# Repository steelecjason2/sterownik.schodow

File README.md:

16 stairs LED controller, and it's easy to extend by connecting just few wires to next TLC5940 PWM LED driver. 

parts not listed in schematics:

2x E18-D80NK Sensor Proximity 3-80cm,

2x microswitches, normal open.

SANPU 12VDC Waterproof LED Power Supply 12V DC 120W 10A IP67

Bluetooth HC-05

LED Strip 12V

PGM5516 photoresistor

2x potentiometer 10k multi-turn type 3/8''

https://www.youtube.com/watch?v=NjSVoOenioQ

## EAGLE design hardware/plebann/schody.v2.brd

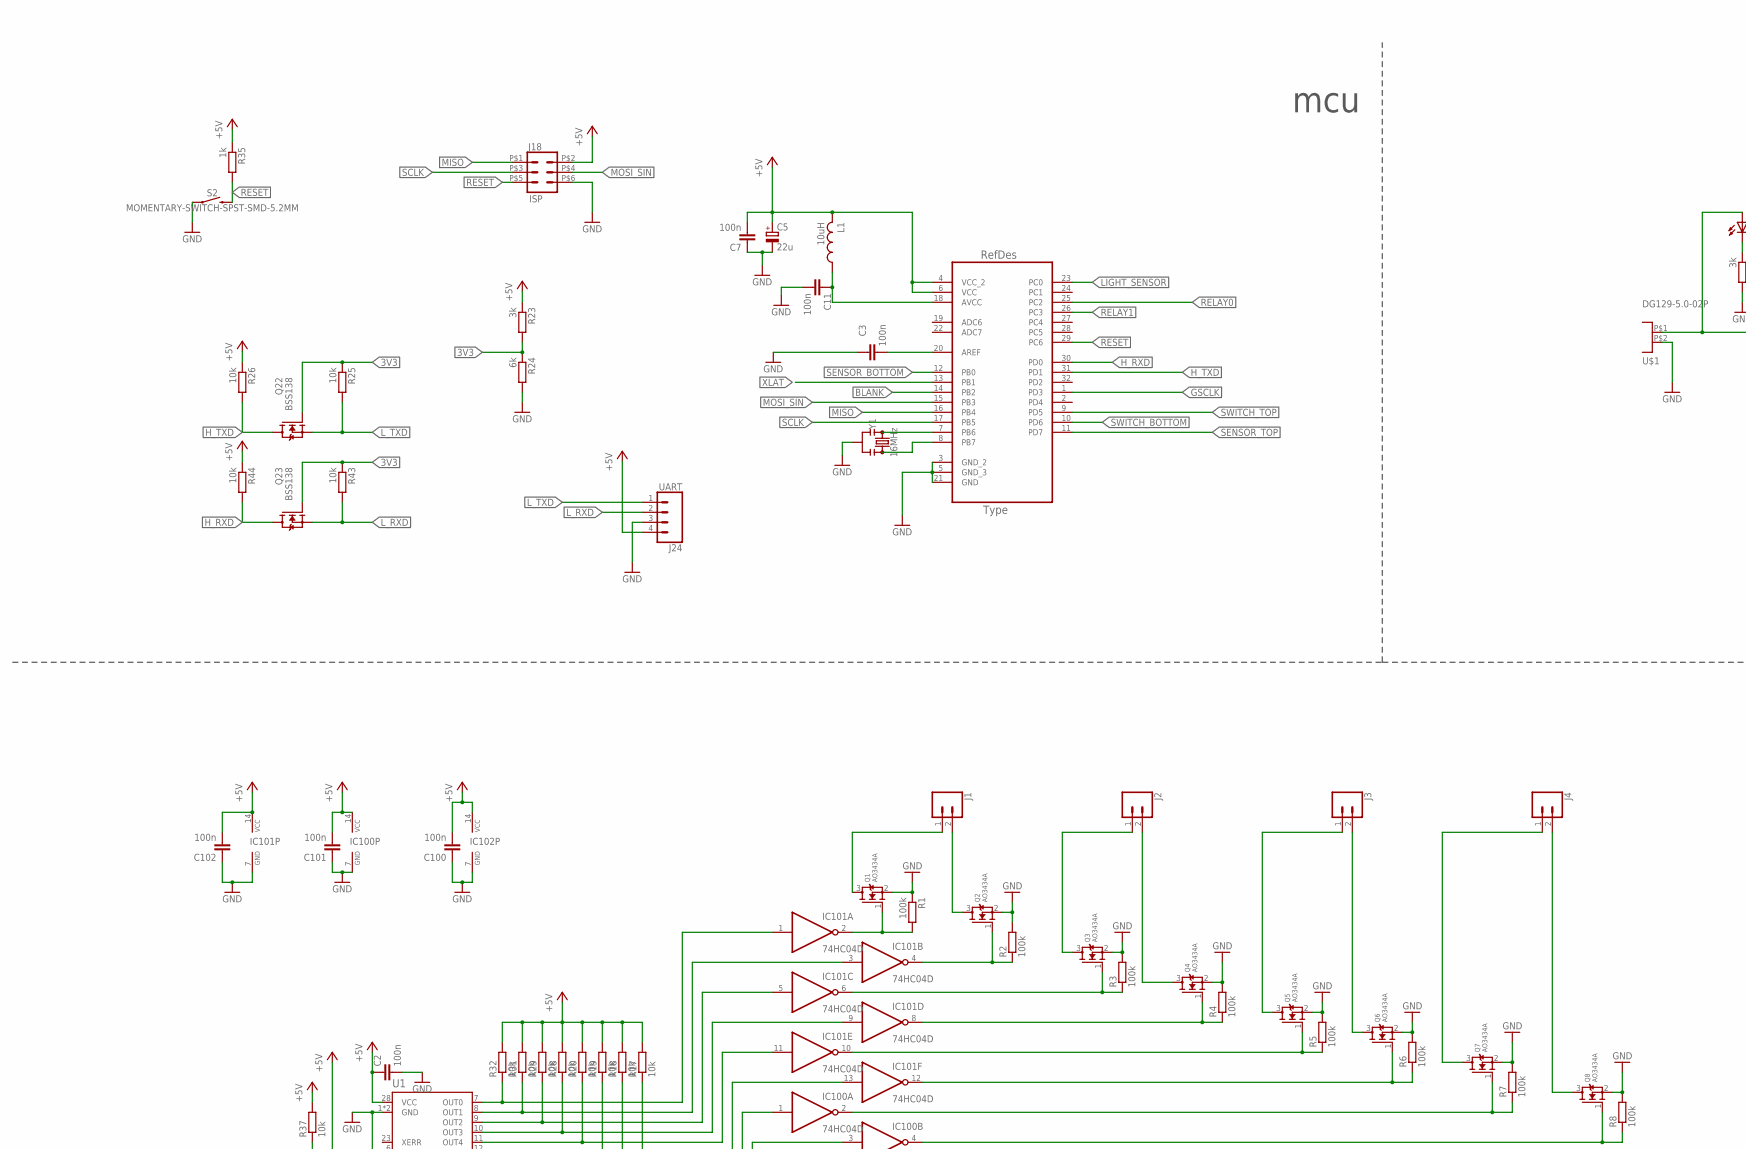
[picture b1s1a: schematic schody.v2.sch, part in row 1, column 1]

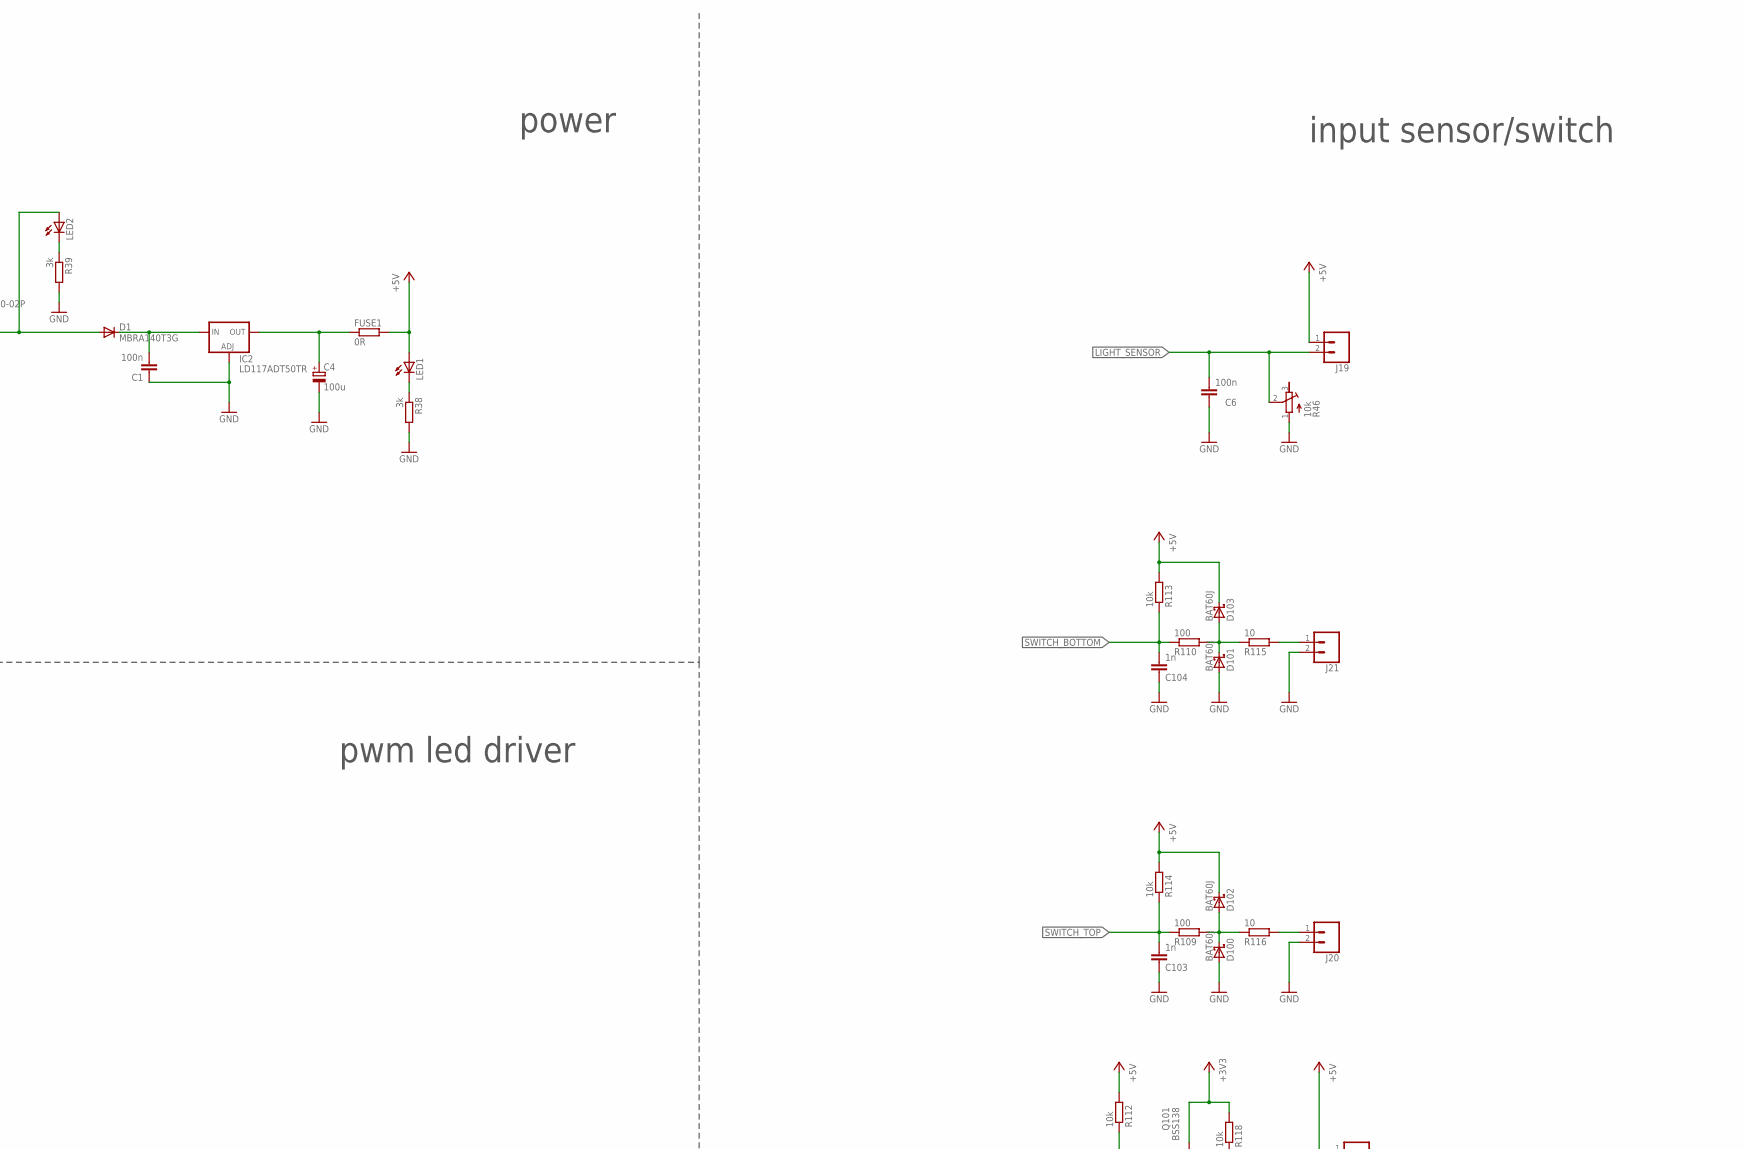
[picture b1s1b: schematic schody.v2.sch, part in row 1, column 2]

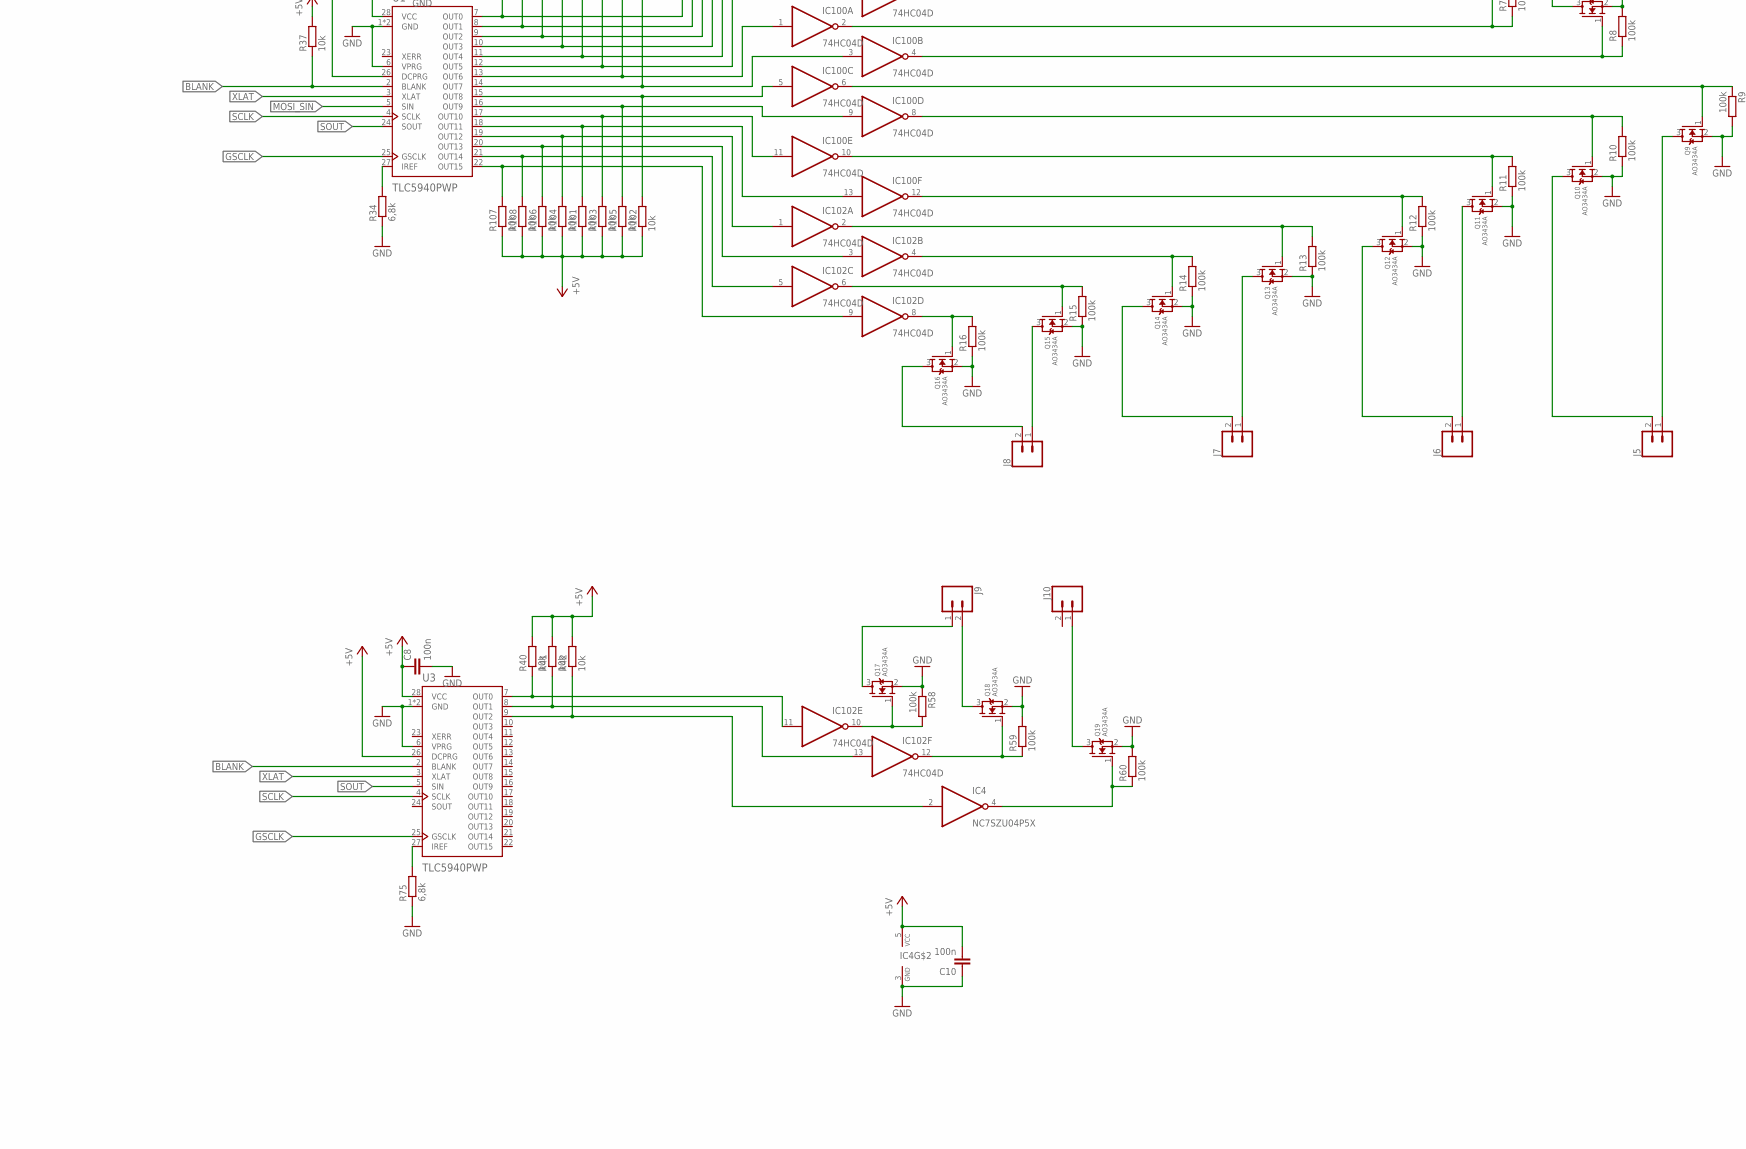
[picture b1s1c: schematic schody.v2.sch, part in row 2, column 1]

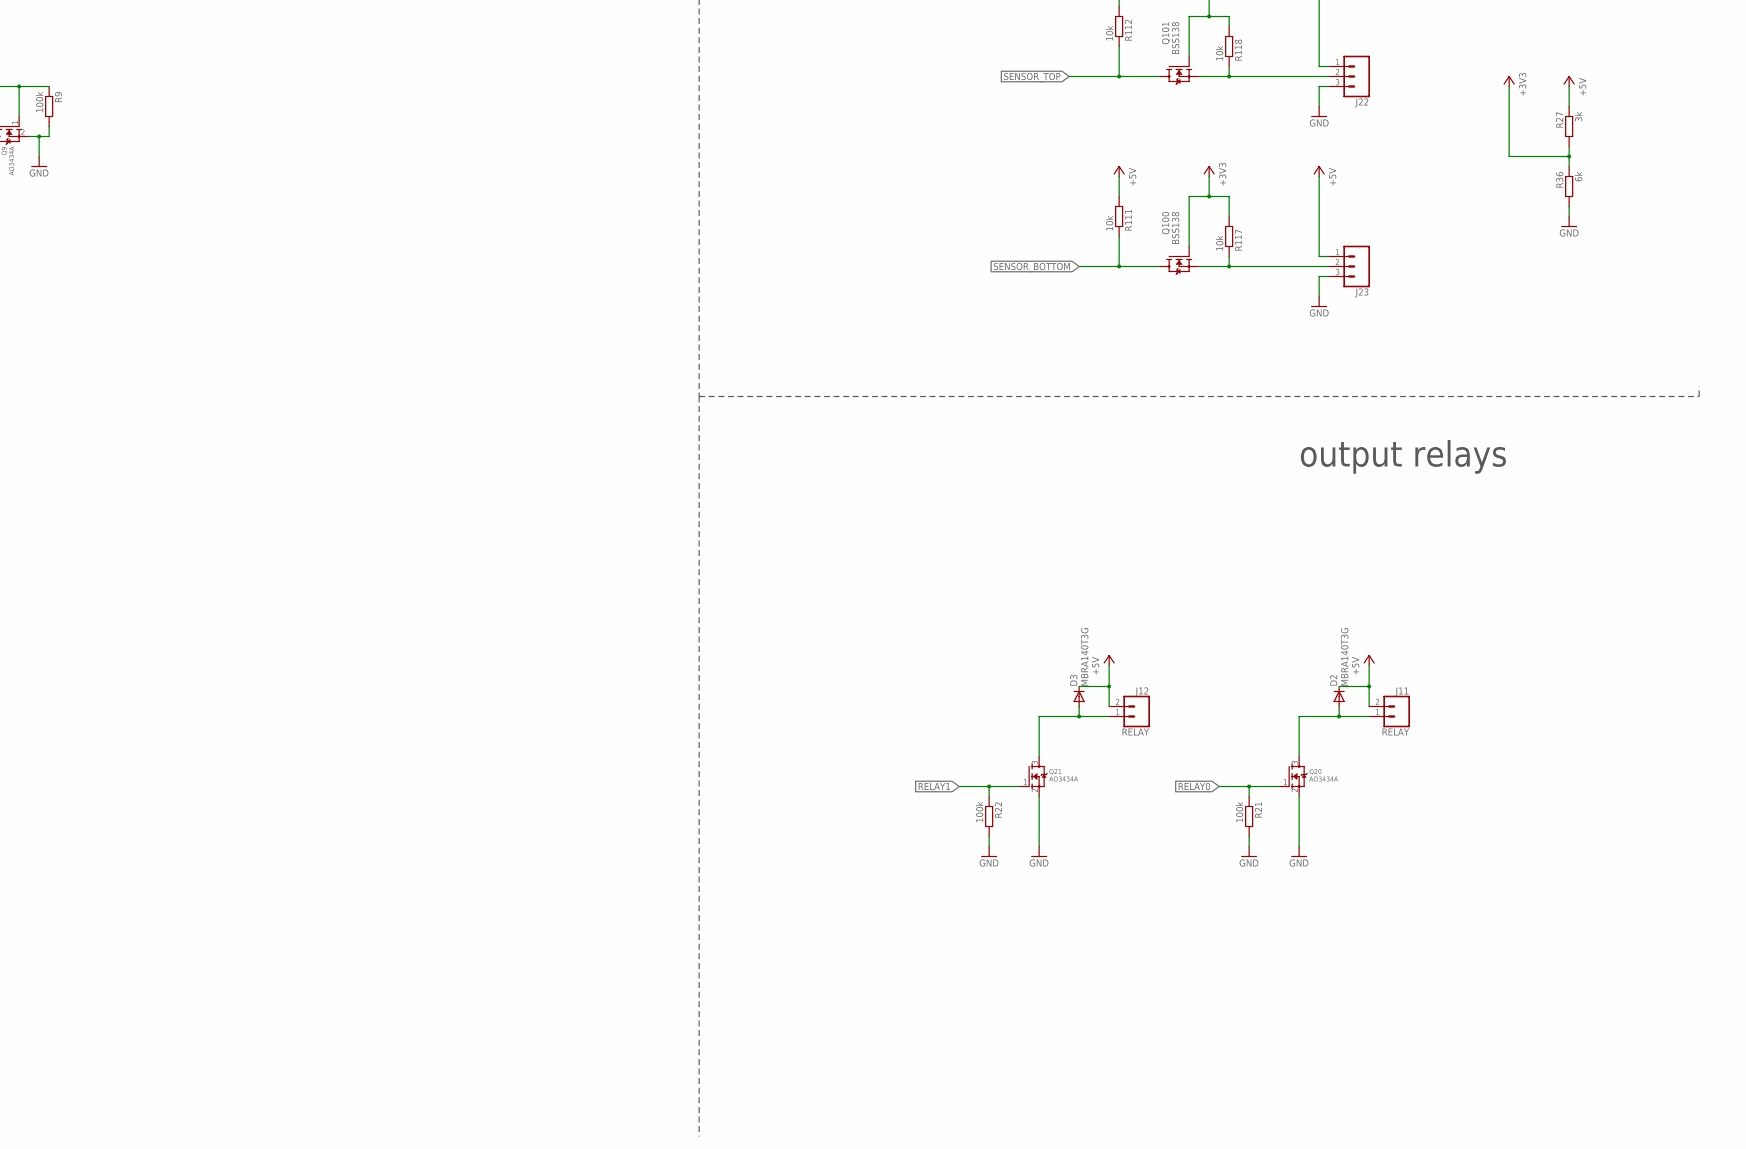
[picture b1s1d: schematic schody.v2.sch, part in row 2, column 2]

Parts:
C1, C2, C8, C10, C100, C101, C102: 100n; C0805K
C3, C6, C7, C11: 100n; C0805
C4: 100u; SMC_D
C5: 22u; SMC_E
C103, C104: 1n; C0805K
D1, D2, D3: MBRA140T3G; DO214BA
D100, D101, D102, D103: BAT60J; SOD323_ST
FUSE1: 0R; M1206
IC2: LD117ADT50TR; DPACK
IC4: NC7SZU04P5X; SC70-5
IC100, IC101, IC102: 74HC04D; SO14
J1, J2, J3, J4, J5, J6, J7, J8, J9, J10, J19, J20, J21: CONN_023.5MM; SCREWTERMINAL-3.5MM-2
J11, J12: RELAY; SCREWTERMINAL-3.5MM-2
J18: ISP; 2X3_POGO
J22, J23: CONN_03SCREW; SCREWTERMINAL-3.5MM-3
J24: UART; 1X04
L1: 10uH; 0805
LED1, LED2: LEDCHIP-LED0805; CHIP-LED0805
Q1, Q2, Q3, Q4, Q5, Q6, Q7, Q8, Q9, Q10, Q11, Q12, Q13, Q14, Q15, Q16, Q17, Q18, Q19, Q20, Q21: AO3434A; SOT23-W
Q22, Q23, Q100, Q101: BSS138; SOT23
R1, R2, R3, R4, R5, R6, R7, R8, R9, R10, R11, R12, R13, R14, R15, R16, R21, R22, R58, R59, R60: 100k; M0805
R17, R18, R19, R20, R25, R26, R28, R29, R31, R32, R37, R40, R41, R42, R43, R44, R101, R102, R103, R104, R105, R106, R107, R108, R111, R112, R113, R114, R117, R118: 10k; M0805
R23, R27, R38, R39: 3k; M0805
R24, R36: 6k; M0805
R34, R75: 6,8k; M0805
R35: 1k; M0805
R46: 10k; RTRIM64W
R109, R110: 100; M0805
R115, R116: 10; M0805
S2: MOMENTARY-SWITCH-SPST-SMD-5.2MM; TACTILE_SWITCH_SMD_5.2MM
U1, U3: TLC5940PWP; HTSSOP28PWP
U2: ATMEGA328P-AU; QFP80P900X900X120-32N
U$1: DG129-5.0-02P
Y1: 16MHz; RESONATOR-SMD-3.2X1.3

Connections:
3V3: Q22.1 (G), Q23.1 (G), R23.2, R24.1, R25.1, R43.1
+3V33: Q100.1 (G), Q101.1 (G), R27.2, R36.1, R117.2, R118.2
+5V: C2.1, C5.+, C7.2, C8.1, C10.2, C100.2, C101.2, C102.2, D2.C, D3.C, D102.C, D103.C, FUSE1.2, IC4.5 (VCC), IC100.14 (VCC), IC101.14 (VCC), IC102.14 (VCC), J11.2, J12.2, J18.P$2 (2), J19.1, J22.1, J23.1, J24.4, L1.2, LED1.A, R17.2, R18.2, R19.2, R20.2, R23.1, R26.1, R27.1, R28.2, R29.2, R31.2, R32.2, R35.1, R37.2, R40.2, R41.2, R42.2, R44.1, R101.1, R102.1, R103.1, R104.1, R105.1, R106.1, R107.1, R108.1, R111.2, R112.2, R113.2, R114.2, U1.26 (DCPRG), U1.28 (VCC), U2.4 (VCC_2), U2.6 (VCC), U3.26 (DCPRG), U3.28 (VCC)
BLANK: R37.1, U1.2 (BLANK), U2.14 (PB2), U3.2 (BLANK)
GND: C1.1, C2.2, C3.1, C4.-, C5.-, C6.1, C7.1, C8.2, C10.1, C11.2, C100.1, C101.1, C102.1, C103.1, C104.1, D100.A, D101.A, IC2.1 (ADJ), IC4.3 (GND), IC100.7 (GND), IC101.7 (GND), IC102.7 (GND), J18.P$6 (6), J20.2, J21.2, J22.3, J23.3, J24.3, Q1.2 (S), Q2.2 (S), Q3.2 (S), Q4.2 (S), Q5.2 (S), Q6.2 (S), Q7.2 (S), Q8.2 (S), Q9.2 (S), Q10.2 (S), Q11.2 (S), Q12.2 (S), Q13.2 (S), Q14.2 (S), Q15.2 (S), Q16.2 (S), Q17.2 (S), Q18.2 (S), Q19.2 (S), Q20.2 (S), Q21.2 (S), R1.1, R2.2, R3.2, R4.2, R5.2, R6.2, R7.2, R8.2, R9.2, R10.1, R11.1, R12.1, R13.1, R14.1, R15.1, R16.1, R21.2, R22.2, R24.2, R34.1, R36.2, R38.2, R39.2, R46.1 (A), R58.1, R59.2, R60.2, R75.1, S2.1, U1.1 (GND), U1.6 (VPRG), U1.EXP (GND), U2.3 (GND_2), U2.5 (GND_3), U2.21 (GND), U3.1 (GND), U3.6 (VPRG), U3.EXP (GND), U$1.P$2, Y1.2
GSCLK: U1.25 (GSCLK), U2.1 (PD3), U3.25 (GSCLK)
H_RXD: Q23.3 (D), R44.2, U2.30 (PD0)
H_TXD: Q22.3 (D), R26.2, U2.31 (PD1)
LIGHT_SENSOR: C6.2, J19.2, R46.2 (S), U2.23 (PC0)
L_RXD: J24.2, Q23.2 (S), R43.2
L_TXD: J24.1, Q22.2 (S), R25.2
MISO: J18.P$1 (1), U2.16 (PB4)
MOSI_SIN: J18.P$4 (4), U1.5 (SIN), U2.15 (PB3)
unnamed: IC101.1 (I), R32.1, U1.7 (OUT0)
unnamed: IC101.3 (I), R31.1, U1.8 (OUT1)
unnamed: IC101.5 (I), R29.1, U1.9 (OUT2)
unnamed: IC101.9 (I), R28.1, U1.10 (OUT3)
unnamed: IC101.11 (I), R20.1, U1.11 (OUT4)
unnamed: IC101.13 (I), R19.1, U1.12 (OUT5)
unnamed: IC100.1 (I), R18.1, U1.13 (OUT6)
unnamed: IC100.3 (I), R17.1, U1.14 (OUT7)
unnamed: IC102.9 (I), R107.2, U1.22 (OUT15)
unnamed: IC101.2 (O), Q1.1 (G), R1.2
unnamed: IC102.3 (I), R106.2, U1.20 (OUT13)
unnamed: IC102.1 (I), R104.2, U1.19 (OUT12)
unnamed: IC100.13 (I), R101.2, U1.18 (OUT11)
unnamed: IC100.11 (I), R103.2, U1.17 (OUT10)
unnamed: IC100.9 (I), R105.2, U1.16 (OUT9)
unnamed: IC100.5 (I), R102.2, U1.15 (OUT8)
unnamed: IC102.5 (I), R108.2, U1.21 (OUT14)
unnamed: J4.2, Q8.3 (D)
unnamed: IC101.6 (O), Q3.1 (G), R3.1
unnamed: J2.2, Q4.3 (D)
unnamed: IC100.4 (O), Q8.1 (G), R8.1
unnamed: J2.1, Q3.3 (D)
unnamed: IC101.8 (O), Q4.1 (G), R4.1
unnamed: IC102.8 (O), Q16.1 (G), R16.2
unnamed: J8.2, Q16.3 (D)
unnamed: J1.1, Q1.3 (D)
unnamed: IC101.10 (O), Q5.1 (G), R5.1
unnamed: J3.1, Q5.3 (D)
unnamed: J9.2, Q18.3 (D)
unnamed: IC101.12 (O), Q6.1 (G), R6.1
unnamed: J5.2, Q10.3 (D)
unnamed: J3.2, Q6.3 (D)
unnamed: IC102.6 (O), Q15.1 (G), R15.2
unnamed: J1.2, Q2.3 (D)
unnamed: J6.1, Q11.3 (D)
unnamed: IC102.4 (O), Q14.1 (G), R14.2
unnamed: J7.2, Q14.3 (D)
unnamed: IC100.8 (O), Q10.1 (G), R10.2
unnamed: IC102.2 (O), Q13.1 (G), R13.2
unnamed: IC100.6 (O), Q9.1 (G), R9.1
unnamed: J7.1, Q13.3 (D)
unnamed: J20.1, R116.2
unnamed: IC100.12 (O), Q12.1 (G), R12.2
unnamed: J6.2, Q12.3 (D)
unnamed: J5.1, Q9.3 (D)
unnamed: IC100.10 (O), Q11.1 (G), R11.2
unnamed: J8.1, Q15.3 (D)
unnamed: J21.1, R115.2
unnamed: C1.2, D1.C, IC2.3 (IN)
unnamed: U2.7 (PB6), Y1.1
unnamed: U2.8 (PB7), Y1.3
unnamed: R34.2, U1.27 (IREF)
unnamed: LED1.C, R38.1
unnamed: D101.C, D103.A, R110.2, R115.1
unnamed: LED2.C, R39.1
unnamed: D100.C, D102.A, R109.2, R116.1
unnamed: IC102.13 (I), R41.1, U3.8 (OUT1)
unnamed: D2.A, J11.1, Q20.3 (D)
unnamed: IC4.2 (I), R42.1, U3.9 (OUT2)
unnamed: J22.2, Q101.2 (S), R118.1
unnamed: J23.2, Q100.2 (S), R117.1
unnamed: C11.1, L1.1, U2.18 (AVCC)
unnamed: C4.+, FUSE1.1, IC2.4 (OUT)
unnamed: C3.2, U2.20 (AREF)
unnamed: IC102.11 (I), R40.1, U3.7 (OUT0)
unnamed: IC101.4 (O), Q2.1 (G), R2.1
unnamed: IC100.2 (O), Q7.1 (G), R7.1
unnamed: D1.A, LED2.A, U$1.P$1
unnamed: J4.1, Q7.3 (D)
unnamed: D3.A, J12.1, Q21.3 (D)
unnamed: IC4.4 (O), Q19.1 (G), R60.1
unnamed: R75.2, U3.27 (IREF)
unnamed: IC102.10 (O), Q17.1 (G), R58.2
unnamed: IC102.12 (O), Q18.1 (G), R59.1
unnamed: J10.1, Q19.3 (D)
unnamed: J9.1, Q17.3 (D)
RELAY0: Q20.1 (G), R21.1, U2.25 (PC2)
RELAY1: Q21.1 (G), R22.1, U2.26 (PC3)
RESET: J18.P$5 (5), R35.2, S2.3 (2), U2.29 (PC6)
SCLK: J18.P$3 (3), U1.4 (SCLK), U2.17 (PB5), U3.4 (SCLK)
SENSOR_BOTTOM: Q100.3 (D), R111.1, U2.12 (PB0)
SENSOR_TOP: Q101.3 (D), R112.1, U2.11 (PD7)
SOUT: U1.24 (SOUT), U3.5 (SIN)
SWITCH_BOTTOM: C104.2, R110.1, R113.1, U2.10 (PD6)
SWITCH_TOP: C103.2, R109.1, R114.1, U2.9 (PD5)
XLAT: U1.3 (XLAT), U2.13 (PB1), U3.3 (XLAT)

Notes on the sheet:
mcu
power
input sensor/switch
pwm led driver
output relays

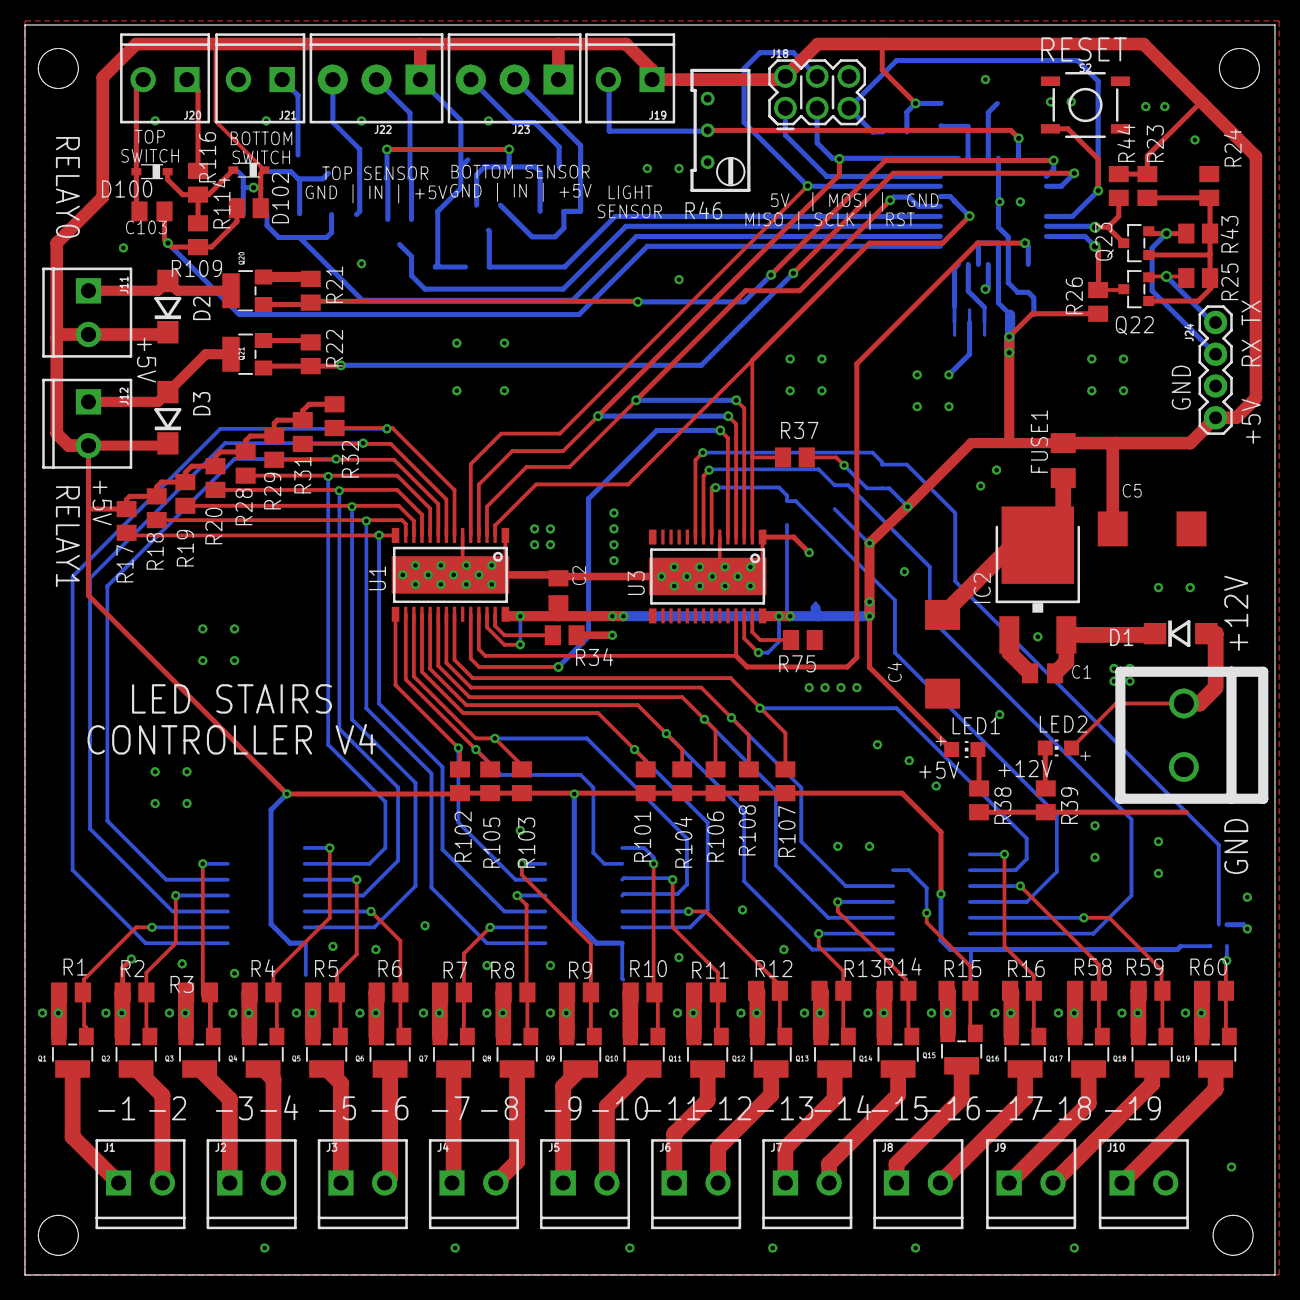
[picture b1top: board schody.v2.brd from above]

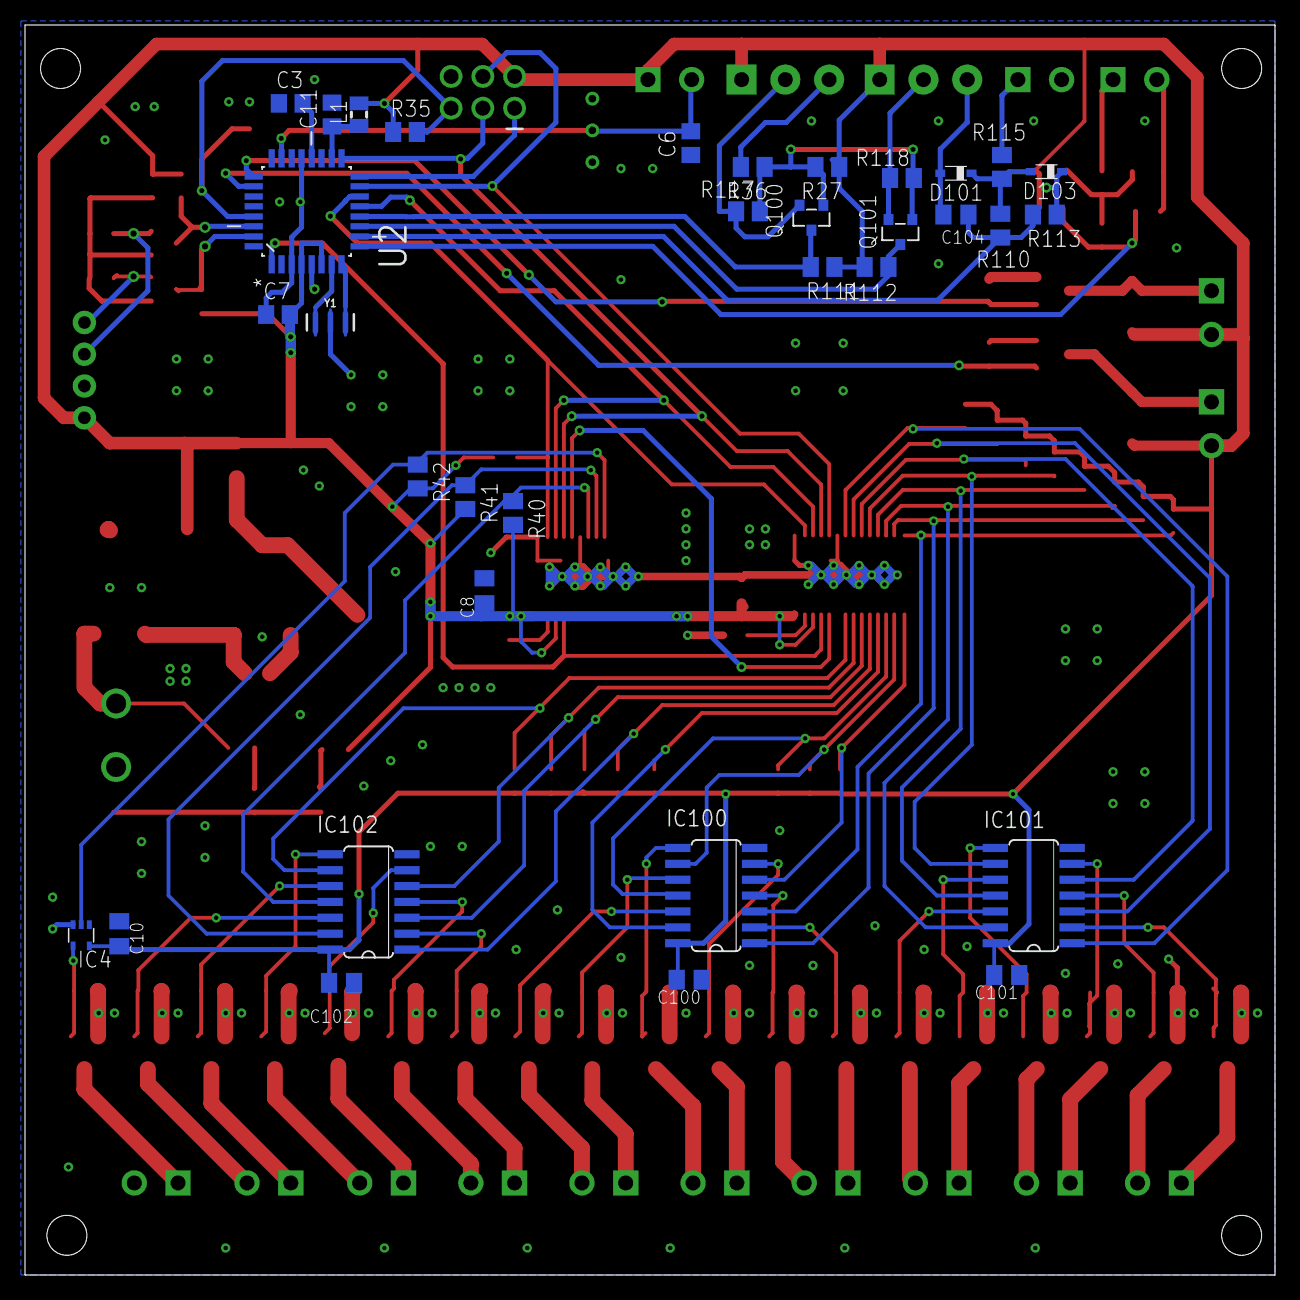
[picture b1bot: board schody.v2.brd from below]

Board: 2 copper layers, 100.0 x 100.0 mm, 146 parts (34 on the bottom side), 99 nets.

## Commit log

2019-10-23 initial code
2019-10-23 pleban ver. 19 stairs, 2 relays
2019-10-23 pdf files

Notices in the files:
parts and their libraries:
SparkFun-Connectors: Licensing: Creative Commons ShareAlike 4.0 International - https://creativecommons.org/licenses/by-sa/4.0
m-pad-2.1: License : GNU General Public License version 2 (see bottom)
